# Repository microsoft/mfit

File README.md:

# mFIT: A Bump-in-the-Wire Tool for Plug-and-Play Analysis of Rowhammer Susceptibility Factors

This repository captures the design and software for mFIT (the **m**emory **f**ault **i**njection **t**ool).

mFIT interposes between the CPU and a DDR4 DIMM and can programmatically suppress the REF command.
This allows researchers to study DRAM DIMMs in the absence of the refresh operation.

Please refer to the Tech Report [MSR-TR-2021-25](https://www.microsoft.com/en-us/research/) for a technical description of mFIT.

# Repository organization

1. [hardware](./hardware) contains the KiCAD schematics and PCB desings,
1. [firmware](./firmware) contains the code that runs on mFIT's control board,
1. [client](./client) contains the client code that interacts with mFIT's control board.

## Contributing

This project welcomes contributions and suggestions.  Most contributions require you to agree to a
Contributor License Agreement (CLA) declaring that you have the right to, and actually do, grant us
the rights to use your contribution. For details, visit https://cla.opensource.microsoft.com.

When you submit a pull request, a CLA bot will automatically determine whether you need to provide
a CLA and decorate the PR appropriately (e.g., status check, comment). Simply follow the instructions
provided by the bot. You will only need to do this once across all repos using our CLA.

This project has adopted the [Microsoft Open Source Code of Conduct](https://opensource.microsoft.com/codeofconduct/).
For more information see the [Code of Conduct FAQ](https://opensource.microsoft.com/codeofconduct/faq/) or
contact [opencode@microsoft.com](mailto:opencode@microsoft.com) with any additional questions or comments.

## Trademarks

This project may contain trademarks or logos for projects, products, or services. Authorized use of Microsoft
trademarks or logos is subject to and must follow
[Microsoft's Trademark & Brand Guidelines](https://www.microsoft.com/en-us/legal/intellectualproperty/trademarks/usage/general).
Use of Microsoft trademarks or logos in modified versions of this project must not cause confusion or imply Microsoft sponsorship.
Any use of third-party trademarks or logos are subject to those third-party's policies.

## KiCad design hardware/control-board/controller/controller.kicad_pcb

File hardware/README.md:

# Intro

This is the hardware description of the mFIT's interposer and the controller board.

There are two [KiCAD](https://www.kicad.org/) projects:

1. the [interposer](./interposer/) that is inserted in the DIMM connector,
1. the [logic controller board](./control-board/) that manipulates the signals on the interposer.

*Note*: The interposer schematic and PCB does not capture the ``HWTRIG_CTL`` signal.
The signal can be read via the additional interposer, by simply
soldering a wire on the ``SDA`` signal.
The ``SDA`` signal is on Pin 285 on a DDR4 RDIMM.

## High-level diagram

## The interposer

## The logic controller board

# Notes on fabrication

The [out](../binary/) folder contains already the gerbers for the interposer.

## The pricing is reasonable

Both boards are double sided and with components on a single side.
The interposer uses two edge connectors, one in which the DIMM is inserted and
one printed on the PCB (gold-fingers).
The interposer has no drill holes.

## Choosing the right PCB finish

While the typical edge connector of a DIMM is gold plated, a low cost option is
to use the silver finish.
Due to its relative flatness, a silver finish makes soldering the edge
female connector easy.

## Use an additional interposer
An additional interposer is required to protect the motherboard.

Typically, cost affordable PCBs are 1.6mm or 1.2mm in thickness.
This makes the edge male connector of the interposer unsuitable for the DIMM
socket on the motherboard.
The DIMM socket expects a 1.4mm thick gold-finger connector.
However, we obtained good results with a PCB of 1.6mm thick and an additional
[DDR4 DIMM extender](https://mfactors.com/jet-5601ah-ddr4-288-extender/).

# Bill of Materials (BOM)

## The interposer
 1. RF switch for the A14 signal, [ADG902](https://www.analog.com/en/products/adg902.html)
 1. digital switch for the ALERTn signal, [SN74AUC1G66](https://www.ti.com/product/SN74AUC1G66)
 1. DDR4 288-Pin, Straddle Mount, 1.2V, [CONN-DDR4-288-SM](http://www.adexelec.com/connectors)

## The controller board
 1. An MCU, [Teensy 3.6](https://www.pjrc.com/store/teensy36.html)
 1. A buffer/level shifter for I/O, based on [TXB0104](https://www.sparkfun.com/products/11771)
 1. Voltage regulator providing 1.2V, based on [AMS1117](http://www.advanced-monolithic.com/pdf/ds1117.pdf)
 1. LEDs, current limiting resistors

## The additional interposer

 1. A [DDR4 DIMM extender](https://mfactors.com/jet-5601ah-ddr4-288-extender/).

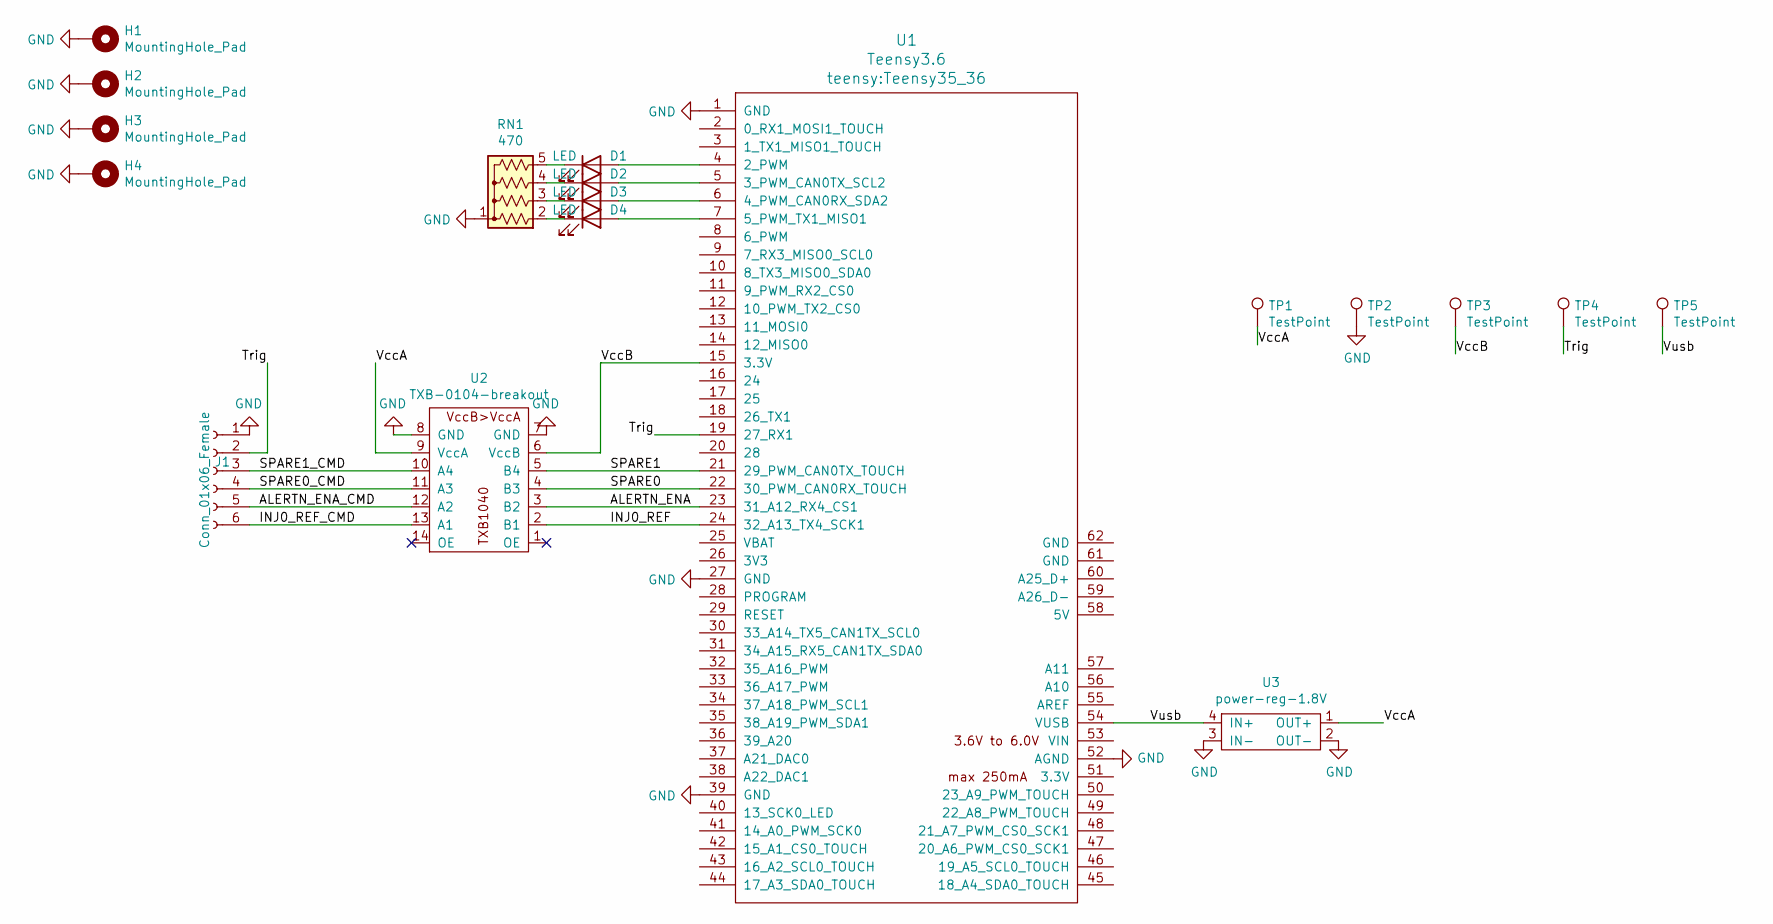
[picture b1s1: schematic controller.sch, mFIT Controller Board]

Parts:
D1, D2, D3, D4: LED; R_0805_2012Metric_Pad1.15x1.40mm_HandSolder
H1, H2, H3, H4: MountingHole_Pad; MountingHole_2.2mm_M2_Pad_Via
J1: Conn_01x06_Female; PinSocket_1x06_P2.54mm_Vertical
RN1: 470; R_Array_SIP5
TP1, TP2, TP3, TP4, TP5: TestPoint; TestPoint_Pad_D1.5mm
U1: Teensy3.6; Teensy35_36
U2: TXB-0104-breakout; TXB0104-breakout
U3: power-reg-1.8V; breakout-power-reg

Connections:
/ALERTN_ENA: U1.23 (31_A12_RX4_CS1), U2.3 (B2)
/ALERTN_ENA_CMD: J1.5, U2.12 (A2)
/INJ0_REF: U1.24 (32_A13_TX4_SCK1), U2.2 (B1)
/INJ0_REF_CMD: J1.6, U2.13 (A1)
/SPARE0: U1.22 (30_PWM_CAN0RX_TOUCH), U2.4 (B3)
/SPARE0_CMD: J1.4, U2.11 (A3)
/SPARE1: U1.21 (29_PWM_CAN0TX_TOUCH), U2.5 (B4)
/SPARE1_CMD: J1.3, U2.10 (A4)
/Trig: J1.2, TP4.1, U1.19 (27_RX1)
/VccA: TP1.1, U2.9 (VccA), U3.1 (OUT+)
/VccB: TP3.1, U1.15 (3.3V), U2.6 (VccB)
/Vusb: TP5.1, U1.54 (VUSB), U3.4 (IN+)
GND: H1.1, H2.1, H3.1, H4.1, J1.1, RN1.1 (common), TP2.1, U1.1 (GND), U1.27 (GND), U1.39 (GND), U1.52 (AGND), U2.7 (GND), U2.8 (GND), U3.2 (OUT-), U3.3 (IN-)
unnamed: D1.1 (K), RN1.5 (R4)
unnamed: D1.2 (A), U1.4 (2_PWM)
unnamed: D2.1 (K), RN1.4 (R3)
unnamed: D2.2 (A), U1.5 (3_PWM_CAN0TX_SCL2)
unnamed: D3.1 (K), RN1.3 (R2)
unnamed: D3.2 (A), U1.6 (4_PWM_CAN0RX_SDA2)
unnamed: D4.1 (K), RN1.2 (R1)
unnamed: D4.2 (A), U1.7 (5_PWM_TX1_MISO1)

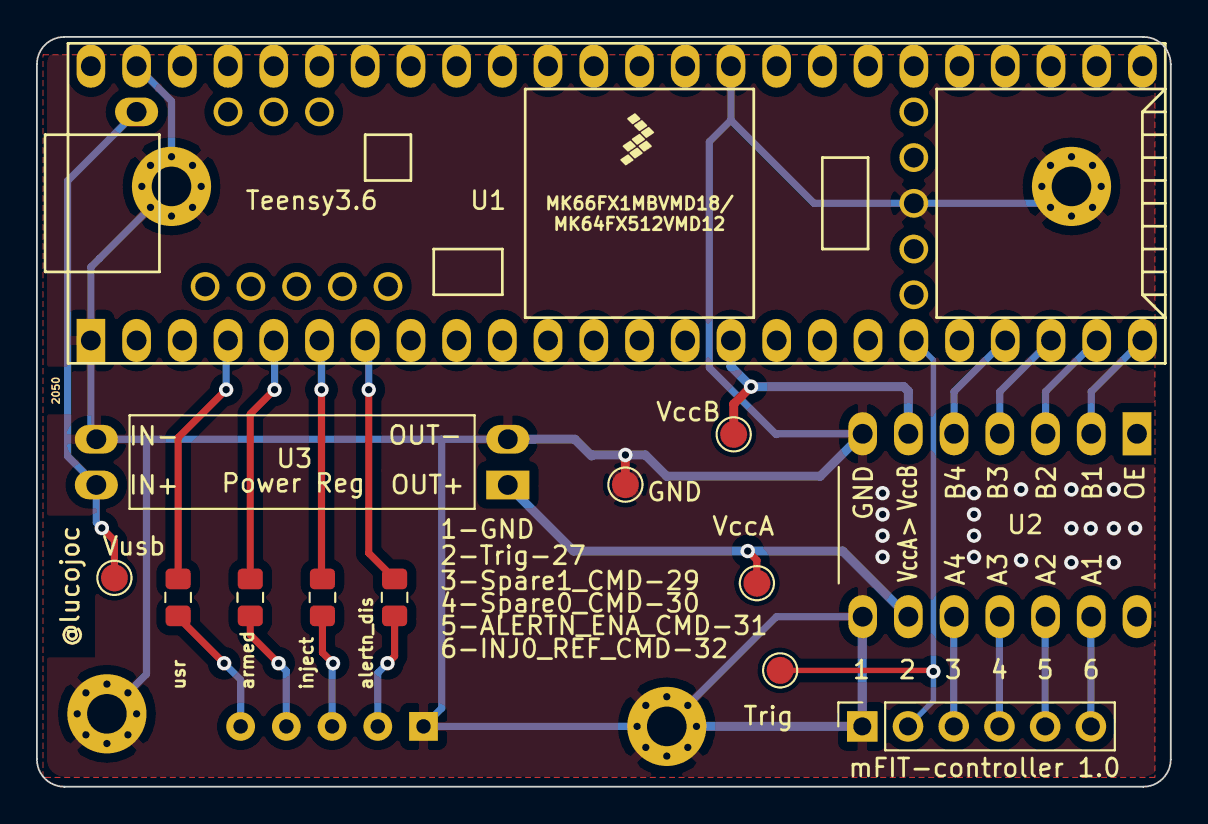
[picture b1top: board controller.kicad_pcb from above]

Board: 2 copper layers, 63.0 x 41.7 mm, 18 parts (1 on the bottom side), 21 nets.

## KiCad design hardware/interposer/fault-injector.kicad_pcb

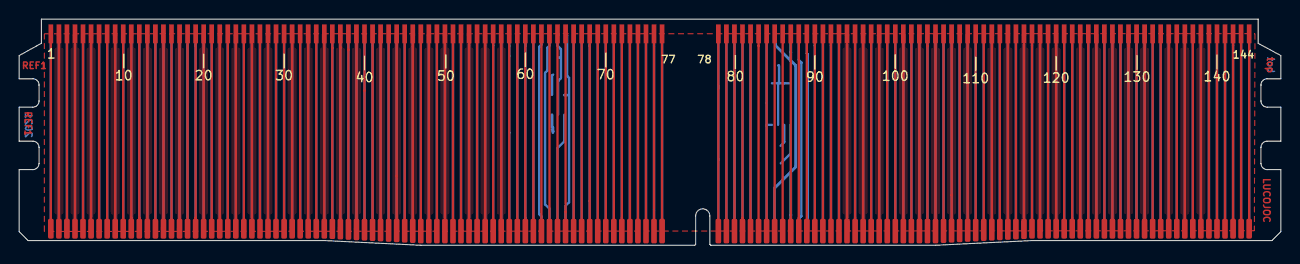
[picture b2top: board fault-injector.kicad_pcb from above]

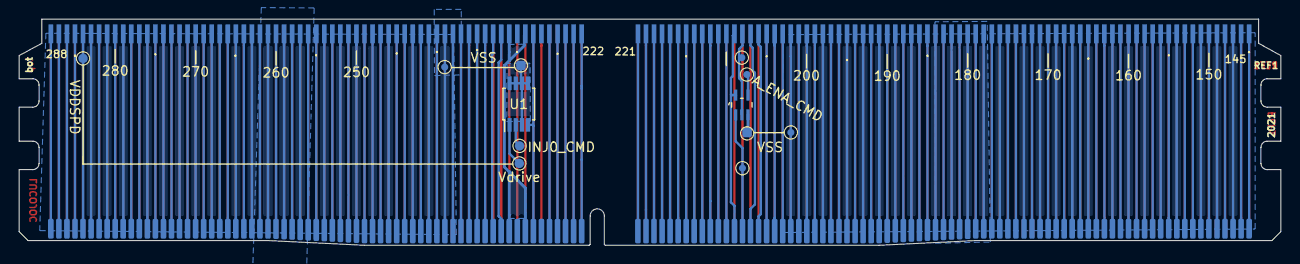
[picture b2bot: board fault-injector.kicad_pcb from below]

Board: 2 copper layers, 133.4 x 23.9 mm, 14 parts (12 on the bottom side), 164 nets.

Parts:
ALERT_n_DIMM: TestPoint_Pad_D1.0mm
ALERT_n_MB: TestPoint_Pad_D1.0mm
A_ENA_CMD: TestPoint_Pad_D1.0mm
INJ0_CMD: TestPoint_Pad_D1.0mm
J1: DDR4_to_MB; ddr4-edge-conn-male
J2: DDR4_to_DIMM; ddr4-edge-conn-female
U1: ADG902BRMZ; MSOP-8_3x3mm_P0.65mm
U2: SN74AUC1G66DCKR
VDDSPD: TestPoint_Pad_D1.0mm
VSS: TestPoint_Pad_D1.0mm
VSS#2, VSS#3, VSS#4: TestPoint_Pad_D1.0mm
Vdrive: TestPoint_Pad_D1.0mm

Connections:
A0_DIMM: J1.79, J2.79
A1_DIMM: J1.72, J2.72
A2_DIMM: J1.216, J2.216
A3_DIMM: J1.71, J2.71
A4_DIMM: J1.214, J2.214
A5_DIMM: J1.213, J2.213
A6_DIMM: J1.69, J2.69
A7_DIMM: J1.211, J2.211
A8_DIMM: J1.68, J2.68
A9_DIMM: J1.66, J2.66
A10_AP_DIMM: J1.225, J2.225
A11_DIMM: J1.210, J2.210
A12_BC_n_DIMM: J1.65, J2.65
A13_DIMM: J1.232, J2.232
A17_DIMM: J1.234, J2.234
ACT_n_DIMM: J1.62, J2.62
ALERT_n_DIMM: ALERT_n_DIMM.1, J2.208, U2.2
ALERT_n_ENA_CMD: A_ENA_CMD.1, U2.4
ALERT_n_MB: ALERT_n_MB.1, J1.208, U2.1
BA0_DIMM: J1.81, J2.81
BA1_DIMM: J1.224, J2.224
BG0_DIMM: J1.63, J2.63
BG1_DIMM: J1.207, J2.207
CAS_n_A15_DIMM: J1.86, J2.86
CB0_DIMM: J1.49, J2.49
CB1_DIMM: J1.194, J2.194
CB2_DIMM: J1.56, J2.56
CB3_DIMM: J1.201, J2.201
CB4_DIMM: J1.47, J2.47
CB5_DIMM: J1.192, J2.192
CB6_DIMM: J1.54, J2.54
CB7_DIMM: J1.199, J2.199
CK0_c_DIMM: J1.75, J2.75
CK0_t_DIMM: J1.74, J2.74
CK1_c_DIMM: J1.219, J2.219
CK1_t_DIMM: J1.218, J2.218
CKE0_DIMM: J1.60, J2.60
CKE1_NC_DIMM: J1.203, J2.203
CS0_n_DIMM: J1.84, J2.84
CS1_n_NC_DIMM: J1.89, J2.89
CS2_n_C0_DIMM: J1.93, J2.93
CS3_n_C1,NC_DIMM: J1.237, J2.237
DQ0_DIMM: J1.5, J2.5
DQ1_DIMM: J1.150, J2.150
DQ2_DIMM: J1.12, J2.12
DQ3_DIMM: J1.157, J2.157
DQ4_DIMM: J1.3, J2.3
DQ5_DIMM: J1.148, J2.148
DQ6_DIMM: J1.10, J2.10
DQ7_DIMM: J1.155, J2.155
DQ8_DIMM: J1.16, J2.16
DQ9_DIMM: J1.161, J2.161
DQ10_DIMM: J1.23, J2.23
DQ11_DIMM: J1.168, J2.168
DQ12_DIMM: J1.14, J2.14
DQ13_DIMM: J1.159, J2.159
DQ14_DIMM: J1.21, J2.21
DQ15_DIMM: J1.166, J2.166
DQ16_DIMM: J1.27, J2.27
DQ17_DIMM: J1.172, J2.172
DQ18_DIMM: J1.34, J2.34
DQ19_DIMM: J1.179, J2.179
DQ20_DIMM: J1.25, J2.25
DQ21_DIMM: J1.170, J2.170
DQ22_DIMM: J1.32, J2.32
DQ23_DIMM: J1.177, J2.177
DQ24_DIMM: J1.38, J2.38
DQ25_DIMM: J1.183, J2.183
DQ26_DIMM: J1.45, J2.45
DQ27_DIMM: J1.190, J2.190
DQ28_DIMM: J1.36, J2.36
DQ29_DIMM: J1.181, J2.181
DQ30_DIMM: J1.43, J2.43
DQ31_DIMM: J1.188, J2.188
DQ32_DIMM: J1.97, J2.97
DQ33_DIMM: J1.242, J2.242
DQ34_DIMM: J1.104, J2.104
DQ35_DIMM: J1.249, J2.249
DQ36_DIMM: J1.95, J2.95
DQ37_DIMM: J1.240, J2.240
DQ38_DIMM: J1.102, J2.102
DQ39_DIMM: J1.247, J2.247
DQ40_DIMM: J1.108, J2.108
DQ41_DIMM: J1.253, J2.253
DQ42_DIMM: J1.115, J2.115
DQ43_DIMM: J1.260, J2.260
DQ44_DIMM: J1.106, J2.106
DQ45_DIMM: J1.251, J2.251
DQ46_DIMM: J1.113, J2.113
DQ47_DIMM: J1.258, J2.258
DQ48_DIMM: J1.119, J2.119
DQ49_DIMM: J1.264, J2.264
DQ50_DIMM: J1.126, J2.126
DQ51_DIMM: J1.271, J2.271
DQ52_DIMM: J1.117, J2.117
DQ53_DIMM: J1.262, J2.262
DQ54_DIMM: J1.124, J2.124
DQ55_DIMM: J1.269, J2.269
DQ56_DIMM: J1.130, J2.130
DQ57_DIMM: J1.275, J2.275
DQ58_DIMM: J1.137, J2.137
DQ59_DIMM: J1.282, J2.282
DQ60_DIMM: J1.128, J2.128
DQ61_DIMM: J1.273, J2.273
DQ62_DIMM: J1.135, J2.135
DQ63_DIMM: J1.280, J2.280
DQS0_c_DIMM: J1.152, J2.152
DQS0_t_DIMM: J1.153, J2.153
DQS1_c_DIMM: J1.163, J2.163
DQS1_t_DIMM: J1.164, J2.164
DQS2_c_DIMM: J1.174, J2.174
DQS2_t_DIMM: J1.175, J2.175
DQS3_c_DIMM: J1.185, J2.185
DQS3_t_DIMM: J1.186, J2.186
DQS4_c_DIMM: J1.244, J2.244
DQS4_t_DIMM: J1.245, J2.245
DQS5_c_DIMM: J1.255, J2.255
DQS5_t_DIMM: J1.256, J2.256
DQS6_c_DIMM: J1.266, J2.266
DQS6_t_DIMM: J1.267, J2.267
DQS7_c_DIMM: J1.277, J2.277
DQS7_t_DIMM: J1.278, J2.278
DQS8_c_DIMM: J1.196, J2.196
DQS8_t_DIMM: J1.197, J2.197
DQS09_c_TDQS9_c_DIMM: J1.8, J2.8
DQS9_t_TDQS9_t_DIMM: J1.7, J2.7
DQS10_c_TDQS10_c_DIMM: J1.19, J2.19
DQS10_t_TDQS10_t_DIMM: J1.18, J2.18
DQS11_c_TDQS11_c_DIMM: J1.30, J2.30
DQS11_t_TDQS11_t_DIMM: J1.29, J2.29
DQS12_c_TDQS12_c_DIMM: J1.41, J2.41
DQS12_t_TDQS12_t_DIMM: J1.40, J2.40
DQS13_c_TDQS13_c_DIMM: J1.100, J2.100
DQS13_t_TDQ13_t_DIMM: J1.99, J2.99
DQS14_c_TDQS14_c_DIMM: J1.111, J2.111
DQS14_t_TDQS14_t_DIMM: J1.110, J2.110
DQS15_c_TDQS15_c_DIMM: J1.122, J2.122
DQS15_t_TDQS15_t_DIMM: J1.121, J2.121
DQS16_c_TDQS16_c_DIMM: J1.133, J2.133
DQS16_t_TDQS16_t_DIMM: J1.132, J2.132
DQS17_c_TDQS17_c_DIMM: J1.52, J2.52
DQS17_t_TDQS17_t_DIMM: J1.51, J2.51
EVENT_n_DIMM: J1.78, J2.78
INJ0_ENA_CMD: INJ0_CMD.1, U1.2
NC_C2_DIMM: J1.235, J2.235
NC_DIMM: J1.1, J1.144, J1.145, J1.205, J1.227, J1.230, J2.1, J2.144, J2.145, J2.205, J2.227, J2.230
ODT0_DIMM: J1.87, J2.87
ODT1_NC_DIMM: J1.91, J2.91
PARITY_DIMM: J1.222, J2.222
RAS_n_A16_DIMM: J1.82, J2.82
RESET_n_DIMM: J1.58, J2.58
SA0_DIMM: J1.139, J2.139
SA1_DIMM: J1.140, J2.140
SA2_DIMM: J1.238, J2.238
SCL_DIMM: J1.141, J2.141
SDA_DIMM: J1.285, J2.285
VDDSPD_DIMM: J1.284, J2.284
VDD_DIMM: J1.59, J1.61, J1.64, J1.67, J1.70, J1.73, J1.76, J1.80, J1.83, J1.85, J1.88, J1.90, J1.92, J1.204, J1.206, J1.209, J1.212, J1.215, J1.217, J1.220, J1.223, J1.226, J1.229, J1.231, J1.233, J1.236, J2.59, J2.61, J2.64, J2.67, J2.70, J2.73, J2.76, J2.80, J2.83, J2.85, J2.88, J2.90, J2.92, J2.204, J2.206, J2.209, J2.212, J2.215, J2.217, J2.220, J2.223, J2.226, J2.229, J2.231, J2.233, J2.236, U2.5
VPP_DIMM: J1.142, J1.143, J1.286, J1.287, J1.288, J2.142, J2.143, J2.286, J2.287, J2.288
VREFCA_DIMM: J1.146, J2.146
VSS_DIMM: J1.2, J1.4, J1.6, J1.9, J1.11, J1.13, J1.15, J1.17, J1.20, J1.22, J1.24, J1.26, J1.28, J1.31, J1.33, J1.35, J1.37, J1.39, J1.42, J1.44, J1.46, J1.48, J1.50, J1.53, J1.55, J1.57, J1.94, J1.96, J1.98, J1.101, J1.103, J1.105, J1.107, J1.109, J1.112, J1.114, J1.116, J1.118, J1.120, J1.123, J1.125, J1.127, J1.129, J1.131, J1.134, J1.136, J1.138, J1.147, J1.149, J1.151, J1.154, J1.156, J1.158, J1.160, J1.162, J1.165, J1.167, J1.169, J1.171, J1.173, J1.176, J1.178, J1.180, J1.182, J1.184, J1.187, J1.189, J1.191, J1.193, J1.195, J1.198, J1.200, J1.202, J1.239, J1.241, J1.243, J1.246, J1.248, J1.250, J1.252, J1.254, J1.257, J1.259, J1.261, J1.263, J1.265, J1.268, J1.270, J1.272, J1.274, J1.276, J1.279, J1.281, J1.283, J2.2, J2.4, J2.6, J2.9, J2.11, J2.13, J2.15, J2.17, J2.20, J2.22, J2.24, J2.26, J2.28, J2.31, J2.33, J2.35, J2.37, J2.39, J2.42, J2.44, J2.46, J2.48, J2.50, J2.53, J2.55, J2.57, J2.94, J2.96, J2.98, J2.101, J2.103, J2.105, J2.107, J2.109, J2.112, J2.114, J2.116, J2.118, J2.120, J2.123, J2.125, J2.127, J2.129, J2.131, J2.134, J2.136, J2.138, J2.147, J2.149, J2.151, J2.154, J2.156, J2.158, J2.160, J2.162, J2.165, J2.167, J2.169, J2.171, J2.173, J2.176, J2.178, J2.180, J2.182, J2.184, J2.187, J2.189, J2.191, J2.193, J2.195, J2.198, J2.200, J2.202, J2.239, J2.241, J2.243, J2.246, J2.248, J2.250, J2.252, J2.254, J2.257, J2.259, J2.261, J2.263, J2.265, J2.268, J2.270, J2.272, J2.274, J2.276, J2.279, J2.281, J2.283, U1.3, U1.5, U1.6, U1.7, U1.8, U2.3, VSS.1, VSS#2.1, VSS#3.1, VSS#4.1
VTT_DIMM: J1.77, J1.221, J2.77, J2.221
Vdrive: U1.1, Vdrive.1
WE_n_A14_DIMM: J1.228, J2.228, U1.4

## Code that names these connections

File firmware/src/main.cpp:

#include "WProgram.h"
#include "usb_desc.h"
#include "usb_dev.h"
#include "usb_rawhid.h"

#include <Arduino.h>

#ifndef USING_MAKEFILE
#error we only support Makefile
#endif

#define HID_TX_TIMEOUT_MS 1

static uint8_t comm_buf[64];
static void
send(void) {
	RawHID.send(&comm_buf[0], HID_TX_TIMEOUT_MS);
}
static void
recv(void)
{
	RawHID.recv(&comm_buf[0], HID_TX_TIMEOUT_MS);
}

#define PIN_LED_TEENSY    13

#define PIN_LED_USR       2
#define PIN_LED_ARMED     3
#define PIN_LED_FI        4
#define PIN_LED_DIS_ALRTN 5

#define PIN_LED PIN_LED_TEENSY

/* these are all configs, e.g. wires setting up, the numbers are
 * are the labels on the PCB
 */
#define PIN_CTRL1 32 /* INJ0_REF_CMD */
#define PIN_CTRL2 31 /* ALERTN_ENA_CMD */
#define PIN_CTRL3 30
#define PIN_TRIG  27

typedef struct __attribute__((packed)) command {
	uint8_t op;
	uint8_t pin;
	union {
		/* param 1 */
		uint32_t delay;
	};
	union {
		/* param 2 */
		uint32_t cnt;
	};
} cmd_t;

typedef struct __attribute__((packed)) response {
	uint8_t code;
	uint8_t payload_len;
	uint8_t payload[0];
} response_t;

static void inline
wait_for_trigger(void)
{
	/* the SDA bus has a pullup */
	while (digitalReadFast(PIN_TRIG)) {}
}

static uint8_t stat_identify = 0;
static cmd_t *cmd = NULL;
static response_t *resp = NULL;
extern "C" int main(void)
{

	//ARM_DEMCR |= ARM_DEMCR_TRCENA;
	//ARM_DWT_CTRL |= ARM_DWT_CTRL_CYCCNTENA;

	/* setup */
	pinMode(PIN_LED, OUTPUT);

	pinMode(PIN_LED_USR, OUTPUT);
	pinMode(PIN_LED_ARMED, OUTPUT);
	pinMode(PIN_LED_FI, OUTPUT);
	pinMode(PIN_LED_DIS_ALRTN, OUTPUT);

	pinMode(PIN_CTRL1, OUTPUT);
	pinMode(PIN_CTRL2, OUTPUT);

	pinMode(PIN_TRIG, INPUT);


	/* alertn is PIN_CTRL2 */
	/* inj is PIN_CTRL1 */
	digitalWriteFast(PIN_CTRL1, LOW);
	digitalWriteFast(PIN_CTRL2, LOW);

	/* by default, ALERTn is disabled */
	digitalWriteFast(PIN_LED_DIS_ALRTN, HIGH);


	cmd = (cmd_t *)&comm_buf[0];
	resp = (response_t *)&comm_buf[0];
#define HARDCODED_MINIMUM_DELAY_US_TO_SENSE_ANOTHER_TRIGGER 50

/* we should get at least one refresh in this interval */
#define HARDCODED_DELAY_US_FOR_RECOVERY 10
#define SETH(pin) digitalWriteFast(pin, HIGH)
#define SETL(pin) digitalWriteFast(pin, LOW)
	while (1) {
		if (cmd->pin != 1 && cmd->pin != 2) {
			goto invalid_pin;
		}
		{
			const uint8_t pin = (cmd->pin == 1) ? PIN_CTRL1 : PIN_CTRL2;
			switch ((unsigned char)cmd->op) {
			case 'h':
					  if (pin == PIN_CTRL2) SETL(PIN_LED_DIS_ALRTN);
					  if (pin == PIN_CTRL1) SETH(PIN_LED_FI);
					  SETH(pin);
					  break;
			case 'l': SETL(pin);
					  if (pin == PIN_CTRL2) SETH(PIN_LED_DIS_ALRTN);
					  if (pin == PIN_CTRL1) SETL(PIN_LED_FI);
					  break;

			case 'd': SETH(PIN_LED_FI); SETH(pin); delay(cmd->delay); SETL(pin); SETL(PIN_LED_FI); break;
			case 'D': SETH(PIN_LED_FI); SETH(pin); delayMicroseconds(cmd->delay); SETL(pin); SETL(PIN_LED_FI); break;

			case 'v':
					  resp->code = 0;
					  resp->payload_len = 5;
					  resp->payload[0] = 'v';
					  resp->payload[1] = 'e';
					  resp->payload[2] = 'r';
					  resp->payload[3] = '2';
					  resp->payload[4] = '3';
					  send();
					  break;
			case 'w': SETH(PIN_LED_ARMED); wait_for_trigger(); SETL(PIN_LED_ARMED); break;

			case 't': SETH(PIN_LED_ARMED); wait_for_trigger(); SETH(PIN_LED_FI);
					  SETH(pin);
					  delay(cmd->delay);
					  SETL(pin);
					  SETL(PIN_LED_FI); SETL(PIN_LED_ARMED);
					  break;
			case 'T': SETH(PIN_LED_ARMED); wait_for_trigger(); SETH(PIN_LED_FI);
					  SETH(pin);
					  delayMicroseconds(cmd->delay);
					  SETL(pin);
					  SETL(PIN_LED_FI); SETL(PIN_LED_ARMED);
					  break;

			case 'a': SETH(PIN_LED_ARMED); wait_for_trigger(); SETH(PIN_LED_FI);
					  SETH(pin);
					  delay(cmd->delay);
					  wait_for_trigger();
					  SETL(pin);
					  SETL(PIN_LED_FI); SETL(PIN_LED_ARMED);
					  break;
			case 'A': SETH(PIN_LED_ARMED); wait_for_trigger(); SETH(PIN_LED_FI);
					  SETH(pin);
					  delayMicroseconds(cmd->delay);
					  wait_for_trigger();
					  SETL(pin);
					  SETL(PIN_LED_FI); SETL(PIN_LED_ARMED);
					  break;

			case 'm':
					  SETH(PIN_LED_ARMED);
					  wait_for_trigger();
					  while (cmd->cnt--) {
						  SETH(PIN_LED_FI);
						  SETH(pin);
						  delayMicroseconds(HARDCODED_MINIMUM_DELAY_US_TO_SENSE_ANOTHER_TRIGGER);
						  wait_for_trigger();
						  SETL(pin);
						  SETL(PIN_LED_FI);
						  delay(cmd->delay);
					  }
					  SETL(PIN_LED_ARMED);
					  break;
			case 'M':
					  SETH(PIN_LED_ARMED);
					  wait_for_trigger();
					  while (cmd->cnt--) {
						  SETH(PIN_LED_FI);
						  SETH(pin);
						  delayMicroseconds(HARDCODED_MINIMUM_DELAY_US_TO_SENSE_ANOTHER_TRIGGER);
						  wait_for_trigger();
						  SETL(pin);
						  SETL(PIN_LED_FI);
						  delayMicroseconds(cmd->delay);
					  }
					  SETL(PIN_LED_ARMED);
					  break;

			case 'r':
					  /* like 'a' but do it in a loop */
					  SETH(PIN_LED_ARMED);
					  while (cmd->cnt--) {
						  wait_for_trigger();
						  SETH(PIN_LED_FI);
						  SETH(pin);
						  delayMicroseconds(HARDCODED_MINIMUM_DELAY_US_TO_SENSE_ANOTHER_TRIGGER);
						  wait_for_trigger();
						  SETL(pin);
						  SETL(PIN_LED_FI);
						  /* this delay should be at least
						   * HARDCODED_MINIMUM_DELAY_US_TO_SENSE_ANOTHER_TRIGGER
						   * to not sense twice the same trigger sig */
						  delay(cmd->delay);
					  }
					  SETL(PIN_LED_ARMED);
					  break;
			case 'R':
					  /* like 'A' but do it in a loop */
					  SETH(PIN_LED_ARMED);
					  while (cmd->cnt--) {
						  wait_for_trigger();
						  SETH(PIN_LED_FI);
						  SETH(pin);
						  delayMicroseconds(HARDCODED_MINIMUM_DELAY_US_TO_SENSE_ANOTHER_TRIGGER);
						  wait_for_trigger();
						  SETL(pin);
						  SETL(PIN_LED_FI);
						  /* this delay should be at least
						   * HARDCODED_MINIMUM_DELAY_US_TO_SENSE_ANOTHER_TRIGGER
						   * to not sense twice the same trigger sig */
						  delayMicroseconds(cmd->delay);
					  }
					  SETL(PIN_LED_ARMED);
					  break;

			case 'f':
					  /* like 'f' but embedd the recovery sequence */
					  SETH(PIN_LED_ARMED);
					  while (cmd->cnt--) {
						  wait_for_trigger();
						  SETH(PIN_LED_FI);
						  SETH(pin);
						  delayMicroseconds(HARDCODED_MINIMUM_DELAY_US_TO_SENSE_ANOTHER_TRIGGER);
						  wait_for_trigger();
						  SETL(pin);
						  SETL(PIN_LED_FI);
						  /* this delay should be at least
						   * HARDCODED_MINIMUM_DELAY_US_TO_SENSE_ANOTHER_TRIGGER
						   * to not sense twice the same trigger sig */
						  delay(cmd->delay);

						  /* Recovery sequence */

						  /* enable alertn */
						  SETH(PIN_CTRL2);
						  SETH(PIN_LED_USR);

						  delayMicroseconds(1);

						  /* do FI */
						  SETH(PIN_LED_FI);
						  SETH(PIN_CTRL1);

						  delayMicroseconds(HARDCODED_DELAY_US_FOR_RECOVERY);

						  /* stop FI */
						  SETL(PIN_LED_FI);
						  SETL(PIN_CTRL1);

						  delayMicroseconds(1);

						  /* disable alertn */
						  SETL(PIN_CTRL2);
						  SETL(PIN_LED_USR);

					  }
					  SETL(PIN_LED_ARMED);
					  break;
			case 'F':
					  /* like 'R' but embedd the recovery sequence */
					  SETH(PIN_LED_ARMED);
					  while (cmd->cnt--) {
						  wait_for_trigger();
						  SETH(PIN_LED_FI);
						  SETH(pin);
						  delayMicroseconds(HARDCODED_MINIMUM_DELAY_US_TO_SENSE_ANOTHER_TRIGGER);
						  wait_for_trigger();
						  SETL(pin);
						  SETL(PIN_LED_FI);
						  /* this delay should be at least
						   * HARDCODED_MINIMUM_DELAY_US_TO_SENSE_ANOTHER_TRIGGER
						   * to not sense twice the same trigger sig */
						  delayMicroseconds(cmd->delay);

						  /* Recovery sequence */

						  /* enable alertn */
						  SETH(PIN_CTRL2);
						  SETH(PIN_LED_USR);

						  delayMicroseconds(1);

						  /* do FI */
						  SETH(PIN_LED_FI);
						  SETH(PIN_CTRL1);

						  delayMicroseconds(HARDCODED_DELAY_US_FOR_RECOVERY);

						  /* stop FI */
						  SETL(PIN_LED_FI);
						  SETL(PIN_CTRL1);

						  delayMicroseconds(1);

						  /* disable alertn */
						  SETL(PIN_CTRL2);
						  SETL(PIN_LED_USR);
					  }
					  SETL(PIN_LED_ARMED);
					  break;

			case 'i':
					  stat_identify = !stat_identify;
					  if (stat_identify) {
						  SETH(PIN_LED_TEENSY);
						  if (cmd->pin == 2) {
							  SETH(PIN_LED_USR);
							  SETH(PIN_LED_ARMED);
							  SETH(PIN_LED_FI);
							  SETH(PIN_LED_DIS_ALRTN);
						  }
					  } else {
						  SETL(PIN_LED_TEENSY);
						  if (cmd->pin == 2) {
							  SETL(PIN_LED_USR);
							  SETL(PIN_LED_ARMED);
							  SETL(PIN_LED_FI);
							  SETL(PIN_LED_DIS_ALRTN);
						  }
					  }
					  break;

			case 'U': asm("bkpt #251"); break;
			default: break;
			};
		}
invalid_pin:
		cmd->op = 0;
		recv();
	}
	return 0;
}

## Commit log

2021-11-04 fixup: add missing Teensy core library submodule
    The submodule seems to be missing from the original release.
2022-07-25 Microsoft mandatory file

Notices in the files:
parts and their libraries:
Copyright 2016 Accelerated Designs. All rights reserved.
